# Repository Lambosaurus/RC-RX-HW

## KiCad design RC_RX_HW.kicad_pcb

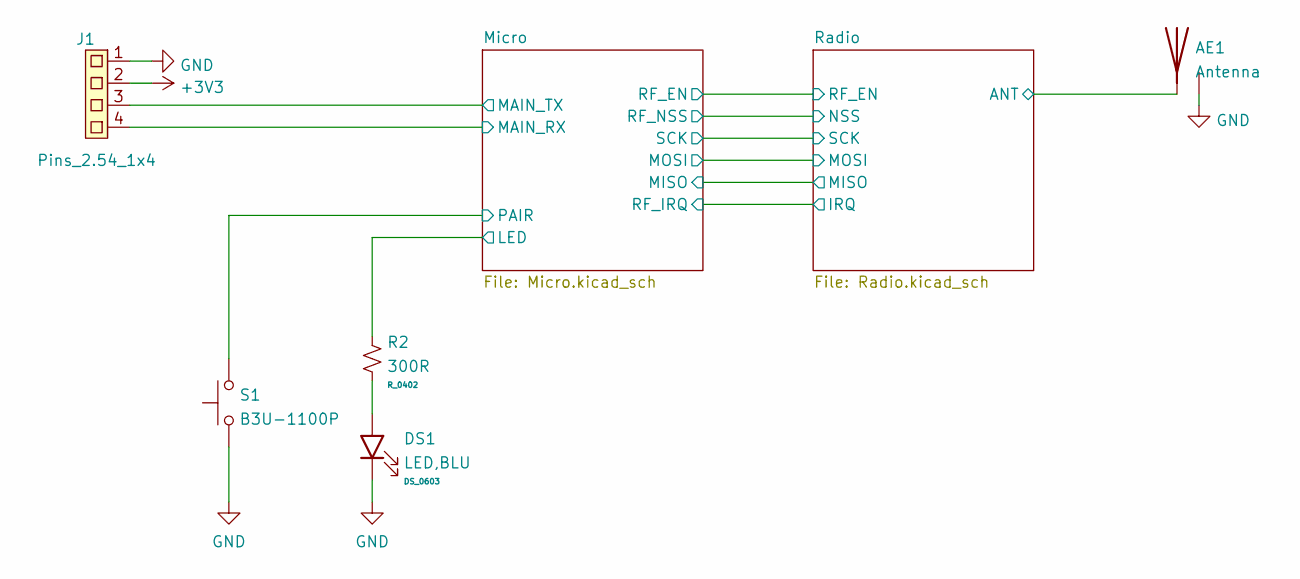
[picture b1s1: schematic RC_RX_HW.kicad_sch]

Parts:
AE1: Antenna; Texas_SWRA117D_2.4GHz_Right
DS1: LED,BLU; DS_0603
J1: Pins_2.54_1x4; Pins-2.54-1x4
R2: 300R; R_0402
S1: B3U-1100P; Button_3.0x2.5

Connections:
+3V3: J1.2; also elsewhere on the board
/Micro/LED: R2.1; also elsewhere on the board
/Micro/MAIN_RX: J1.4; also elsewhere on the board
/Micro/MAIN_TX: J1.3; also elsewhere on the board
/Micro/PAIR: S1.2; also elsewhere on the board
/Radio/ANT: AE1.1 (A); also elsewhere on the board
GND: AE1.2 (G), DS1.1 (K), J1.1, S1.1; also elsewhere on the board
unnamed: DS1.2 (A), R2.2

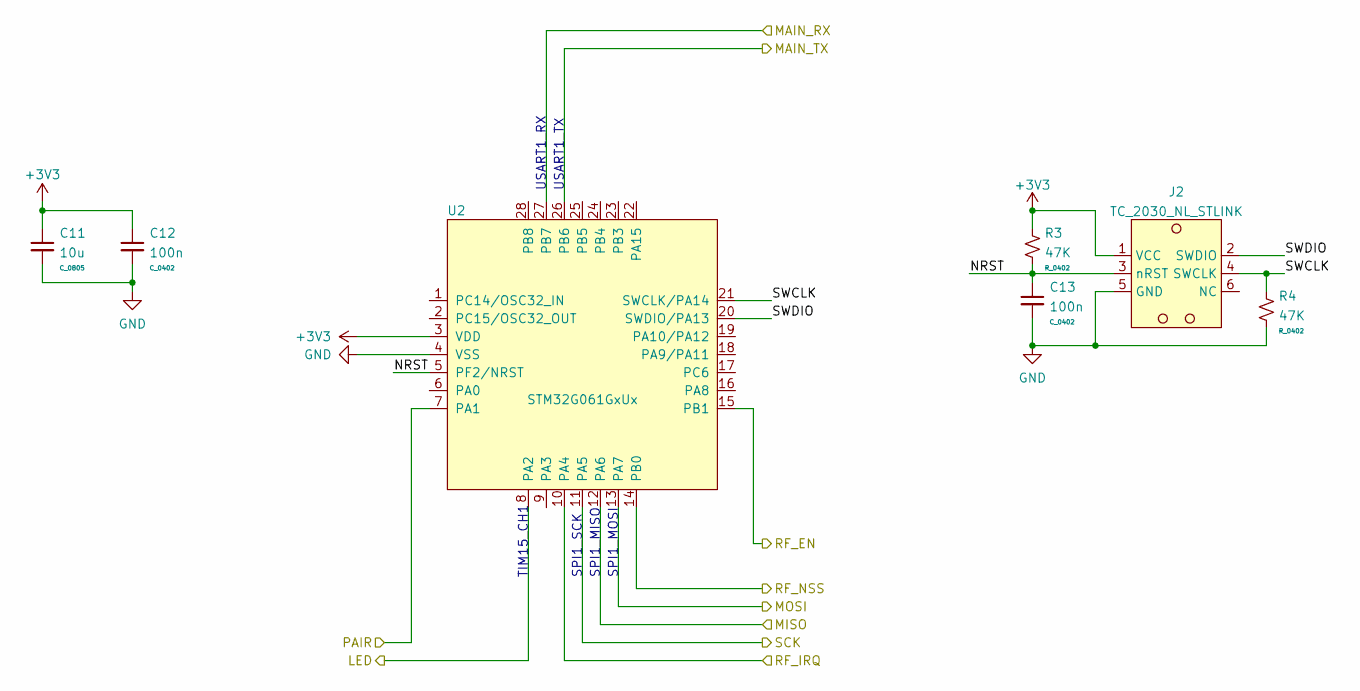
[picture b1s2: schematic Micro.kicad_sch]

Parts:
C11: 10u; C_0805
C12, C13: 100n; C_0402
J2: TC_2030_NL_STLINK; TagConnect_2030_NL
R3, R4: 47K; R_0402
U2: STM32G061GxUx; QFN28_05_4x4

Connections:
+3V3: C11.1, C12.1, J2.1 (VCC), R3.1, U2.3 (VDD); also elsewhere on the board
/Micro/LED: U2.8 (PA2); also elsewhere on the board
/Micro/MAIN_RX: U2.27 (PB7); also elsewhere on the board
/Micro/MAIN_TX: U2.26 (PB6); also elsewhere on the board
/Micro/MISO: U2.12 (PA6); also elsewhere on the board
/Micro/MOSI: U2.13 (PA7); also elsewhere on the board
/Micro/NRST: C13.1, J2.3 (nRST), R3.2, U2.5 (PF2/NRST)
/Micro/PAIR: U2.7 (PA1); also elsewhere on the board
/Micro/RF_EN: U2.15 (PB1); also elsewhere on the board
/Micro/RF_IRQ: U2.10 (PA4); also elsewhere on the board
/Micro/RF_NSS: U2.14 (PB0); also elsewhere on the board
/Micro/SCK: U2.11 (PA5); also elsewhere on the board
/Micro/SWCLK: J2.4 (SWCLK), R4.1, U2.21 (SWCLK/PA14)
/Micro/SWDIO: J2.2 (SWDIO), U2.20 (SWDIO/PA13)
GND: C11.2, C12.2, C13.2, J2.5 (GND), R4.2, U2.4 (VSS); also elsewhere on the board

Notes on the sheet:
USART1_TX
USART1_RX
SPI1_SCK
TIM15_CH1
SPI1_MOSI
SPI1_MISO

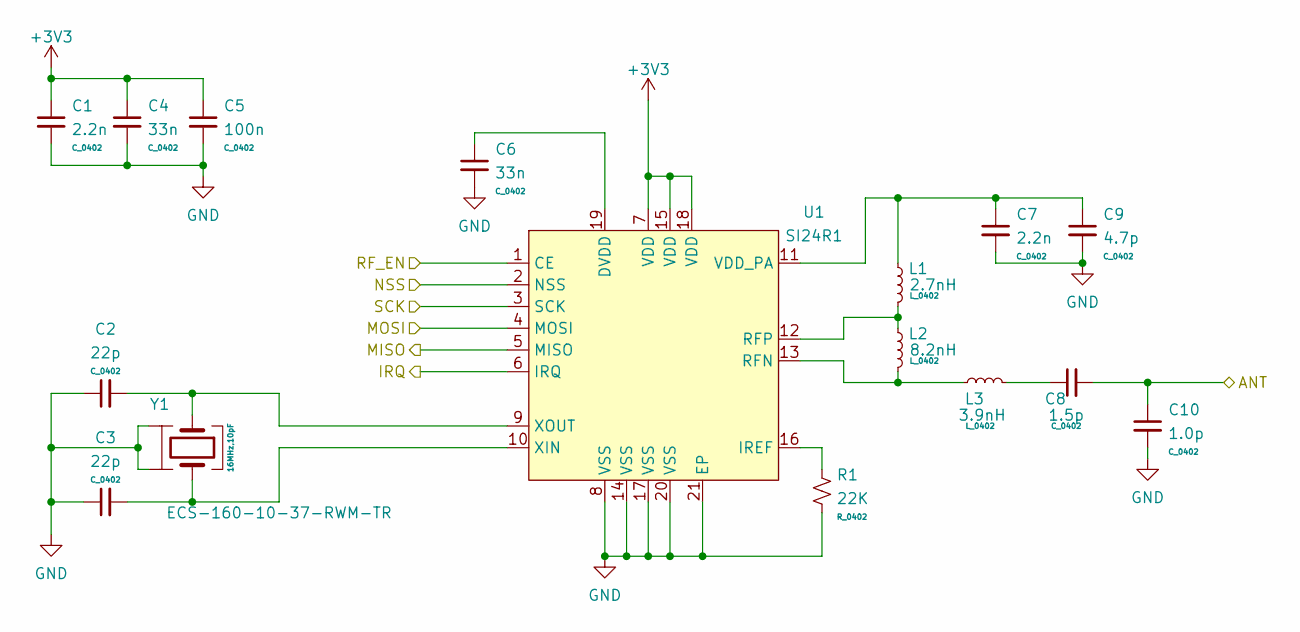
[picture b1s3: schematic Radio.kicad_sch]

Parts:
C1, C7: 2.2n; C_0402
C2, C3: 22p; C_0402
C4, C6: 33n; C_0402
C5: 100n; C_0402
C8: 1.5p; C_0402
C9: 4.7p; C_0402
C10: 1.0p; C_0402
L1: 2.7nH; FB_0402
L2: 8.2nH; FB_0402
L3: 3.9nH; FB_0402
R1: 22K; R_0402
U1: SI24R1; QFN20_05_4x4_EP
Y1: ECS-160-10-37-RWM-TR; Crystal_SMD4_2.0x1.6

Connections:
+3V3: C1.1, C4.1, C5.1, U1.7 (VDD), U1.15 (VDD), U1.18 (VDD); also elsewhere on the board
/Micro/MISO: U1.5 (MISO); also elsewhere on the board
/Micro/MOSI: U1.4 (MOSI); also elsewhere on the board
/Micro/RF_EN: U1.1 (CE); also elsewhere on the board
/Micro/RF_IRQ: U1.6 (IRQ); also elsewhere on the board
/Micro/RF_NSS: U1.2 (NSS); also elsewhere on the board
/Micro/SCK: U1.3 (SCK); also elsewhere on the board
/Radio/ANT: C8.2, C10.1; also elsewhere on the board
GND: C1.2, C2.1, C3.1, C4.2, C5.2, C6.2, C7.2, C9.2, C10.2, R1.2, U1.8 (VSS), U1.14 (VSS), U1.17 (VSS), U1.20 (VSS), U1.21 (EP), Y1.2, Y1.4; also elsewhere on the board
unnamed: C2.2, U1.9 (XOUT), Y1.1
unnamed: C3.2, U1.10 (XIN), Y1.3
unnamed: C6.1, U1.19 (DVDD)
unnamed: C7.1, C9.1, L1.1, U1.11 (VDD_PA)
unnamed: C8.1, L3.2
unnamed: L1.2, L2.1, U1.12 (RFP)
unnamed: L2.2, L3.1, U1.13 (RFN)
unnamed: R1.1, U1.16 (IREF)

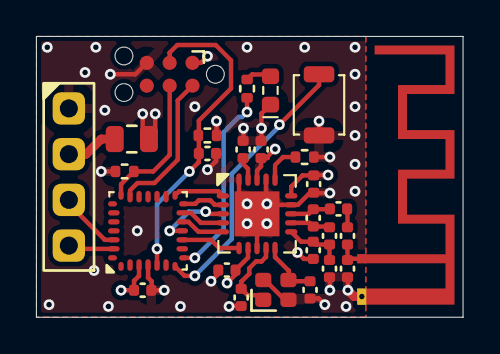
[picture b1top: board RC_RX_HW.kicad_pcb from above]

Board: 4 copper layers, 23.7 x 15.6 mm, 28 parts (0 on the bottom side), 25 nets.

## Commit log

2023-01-03 First design pass
